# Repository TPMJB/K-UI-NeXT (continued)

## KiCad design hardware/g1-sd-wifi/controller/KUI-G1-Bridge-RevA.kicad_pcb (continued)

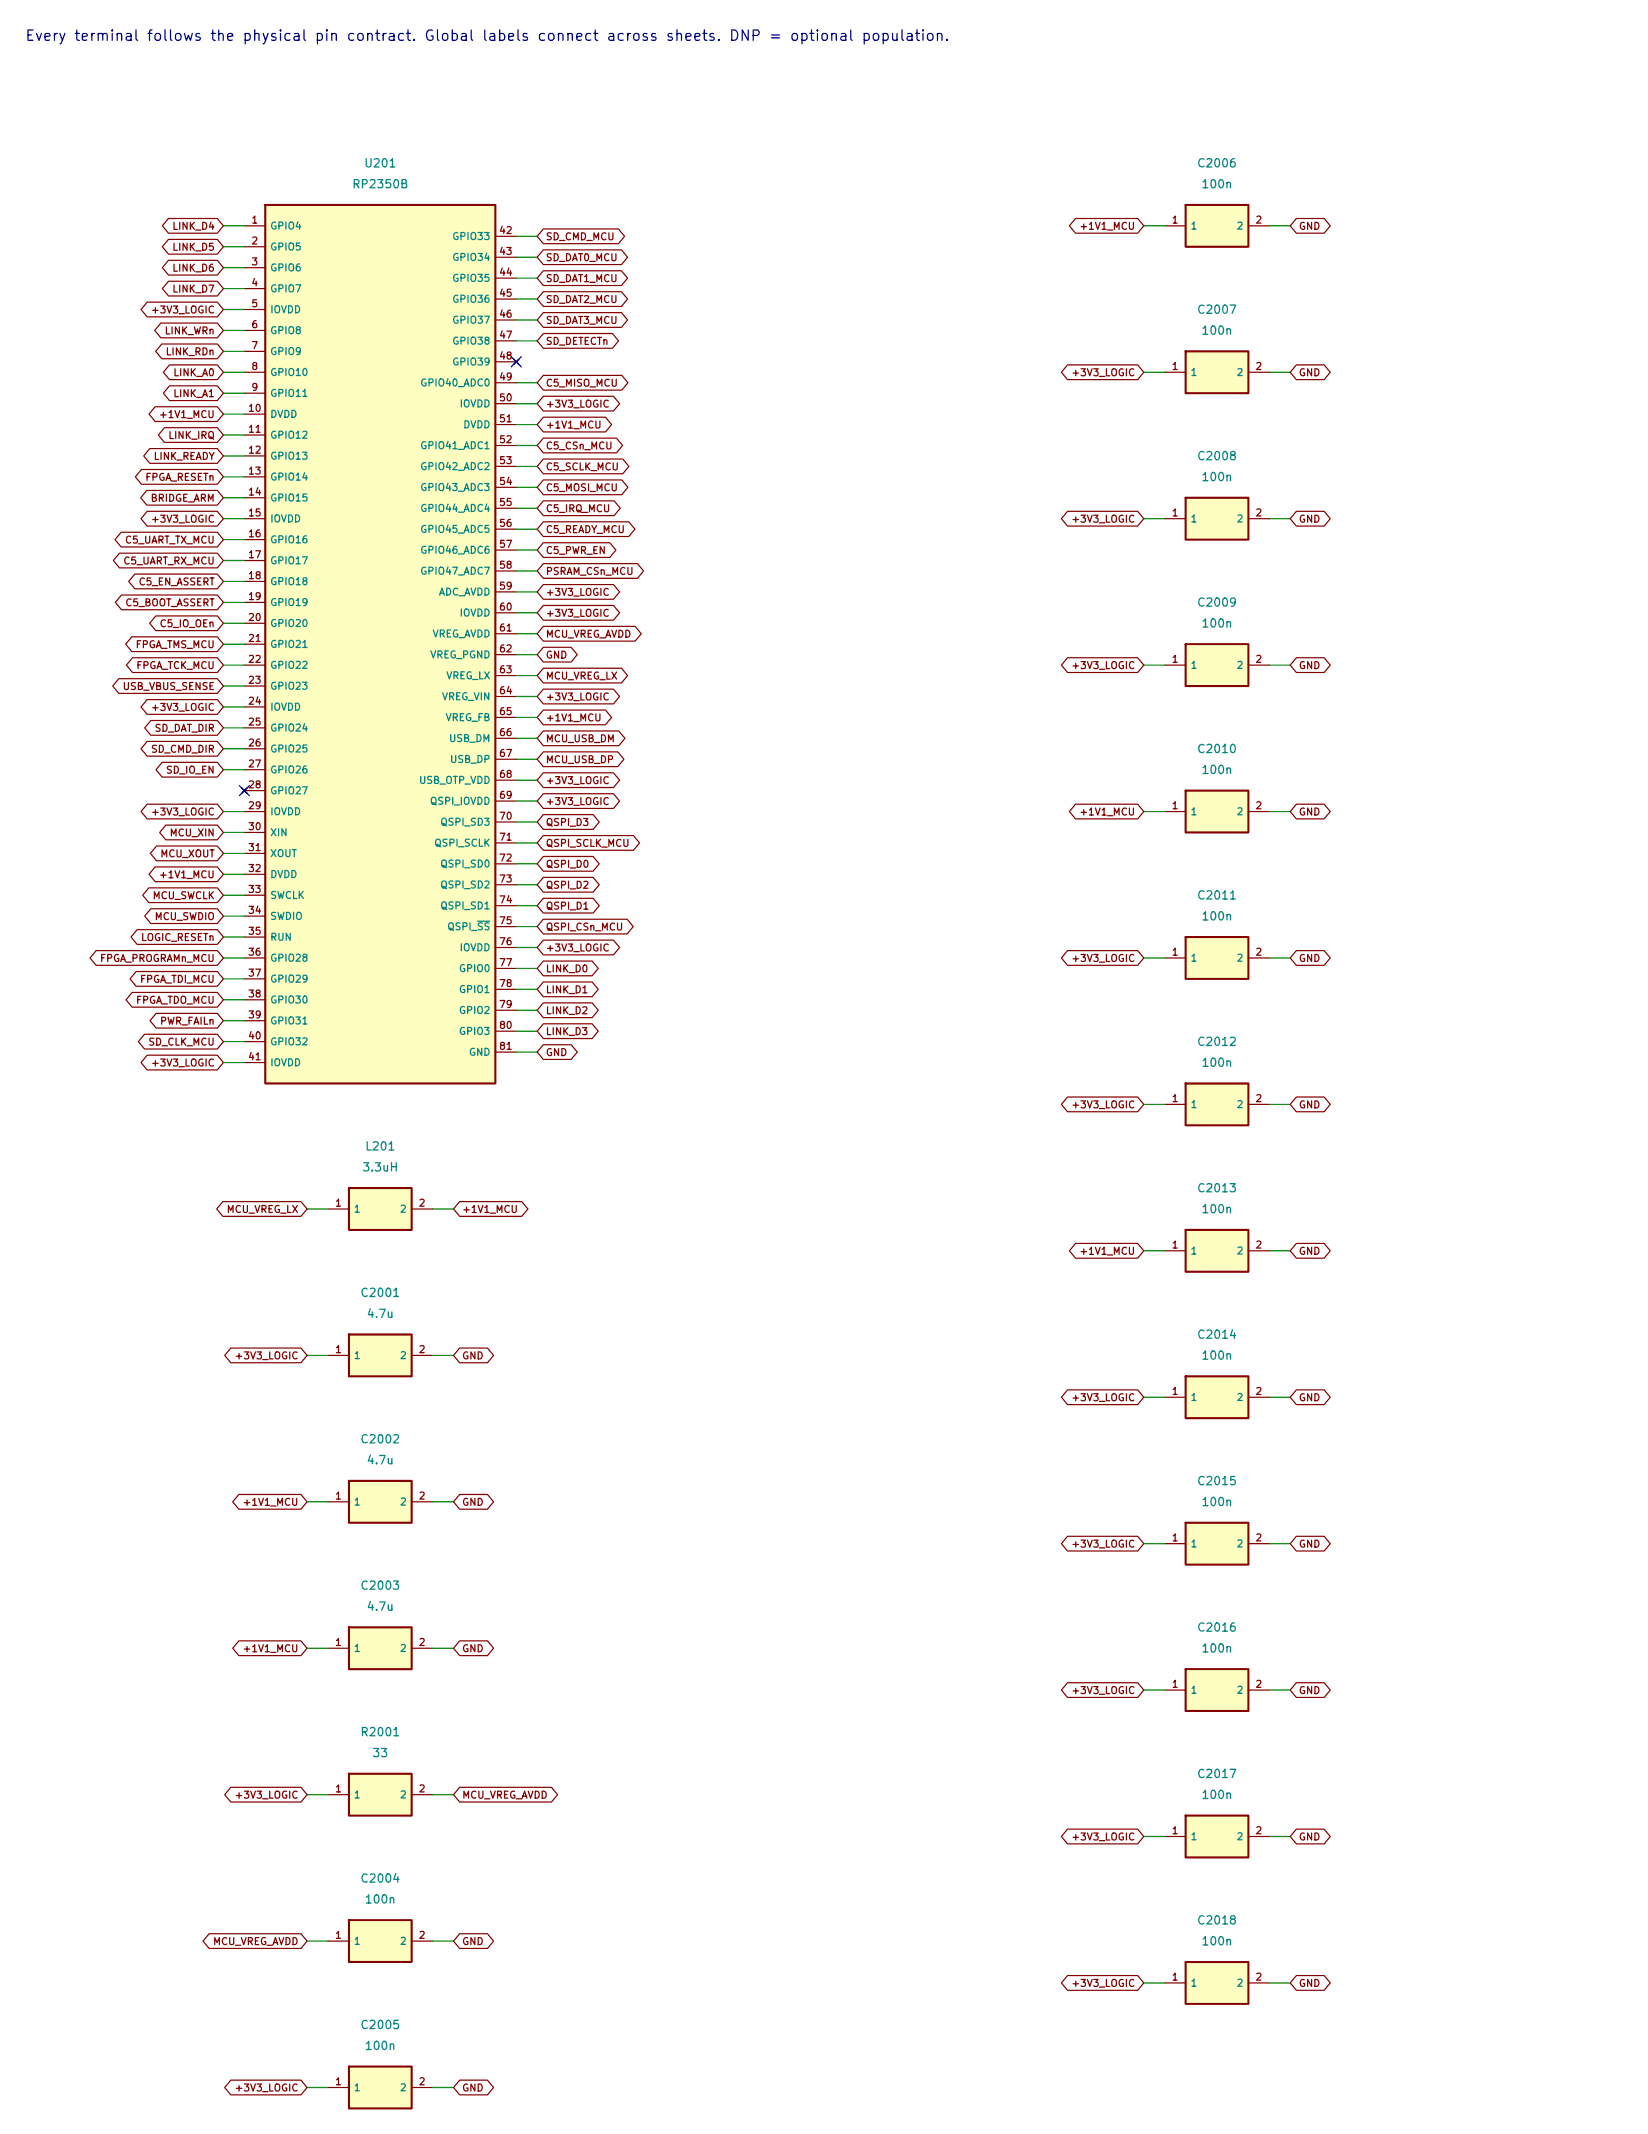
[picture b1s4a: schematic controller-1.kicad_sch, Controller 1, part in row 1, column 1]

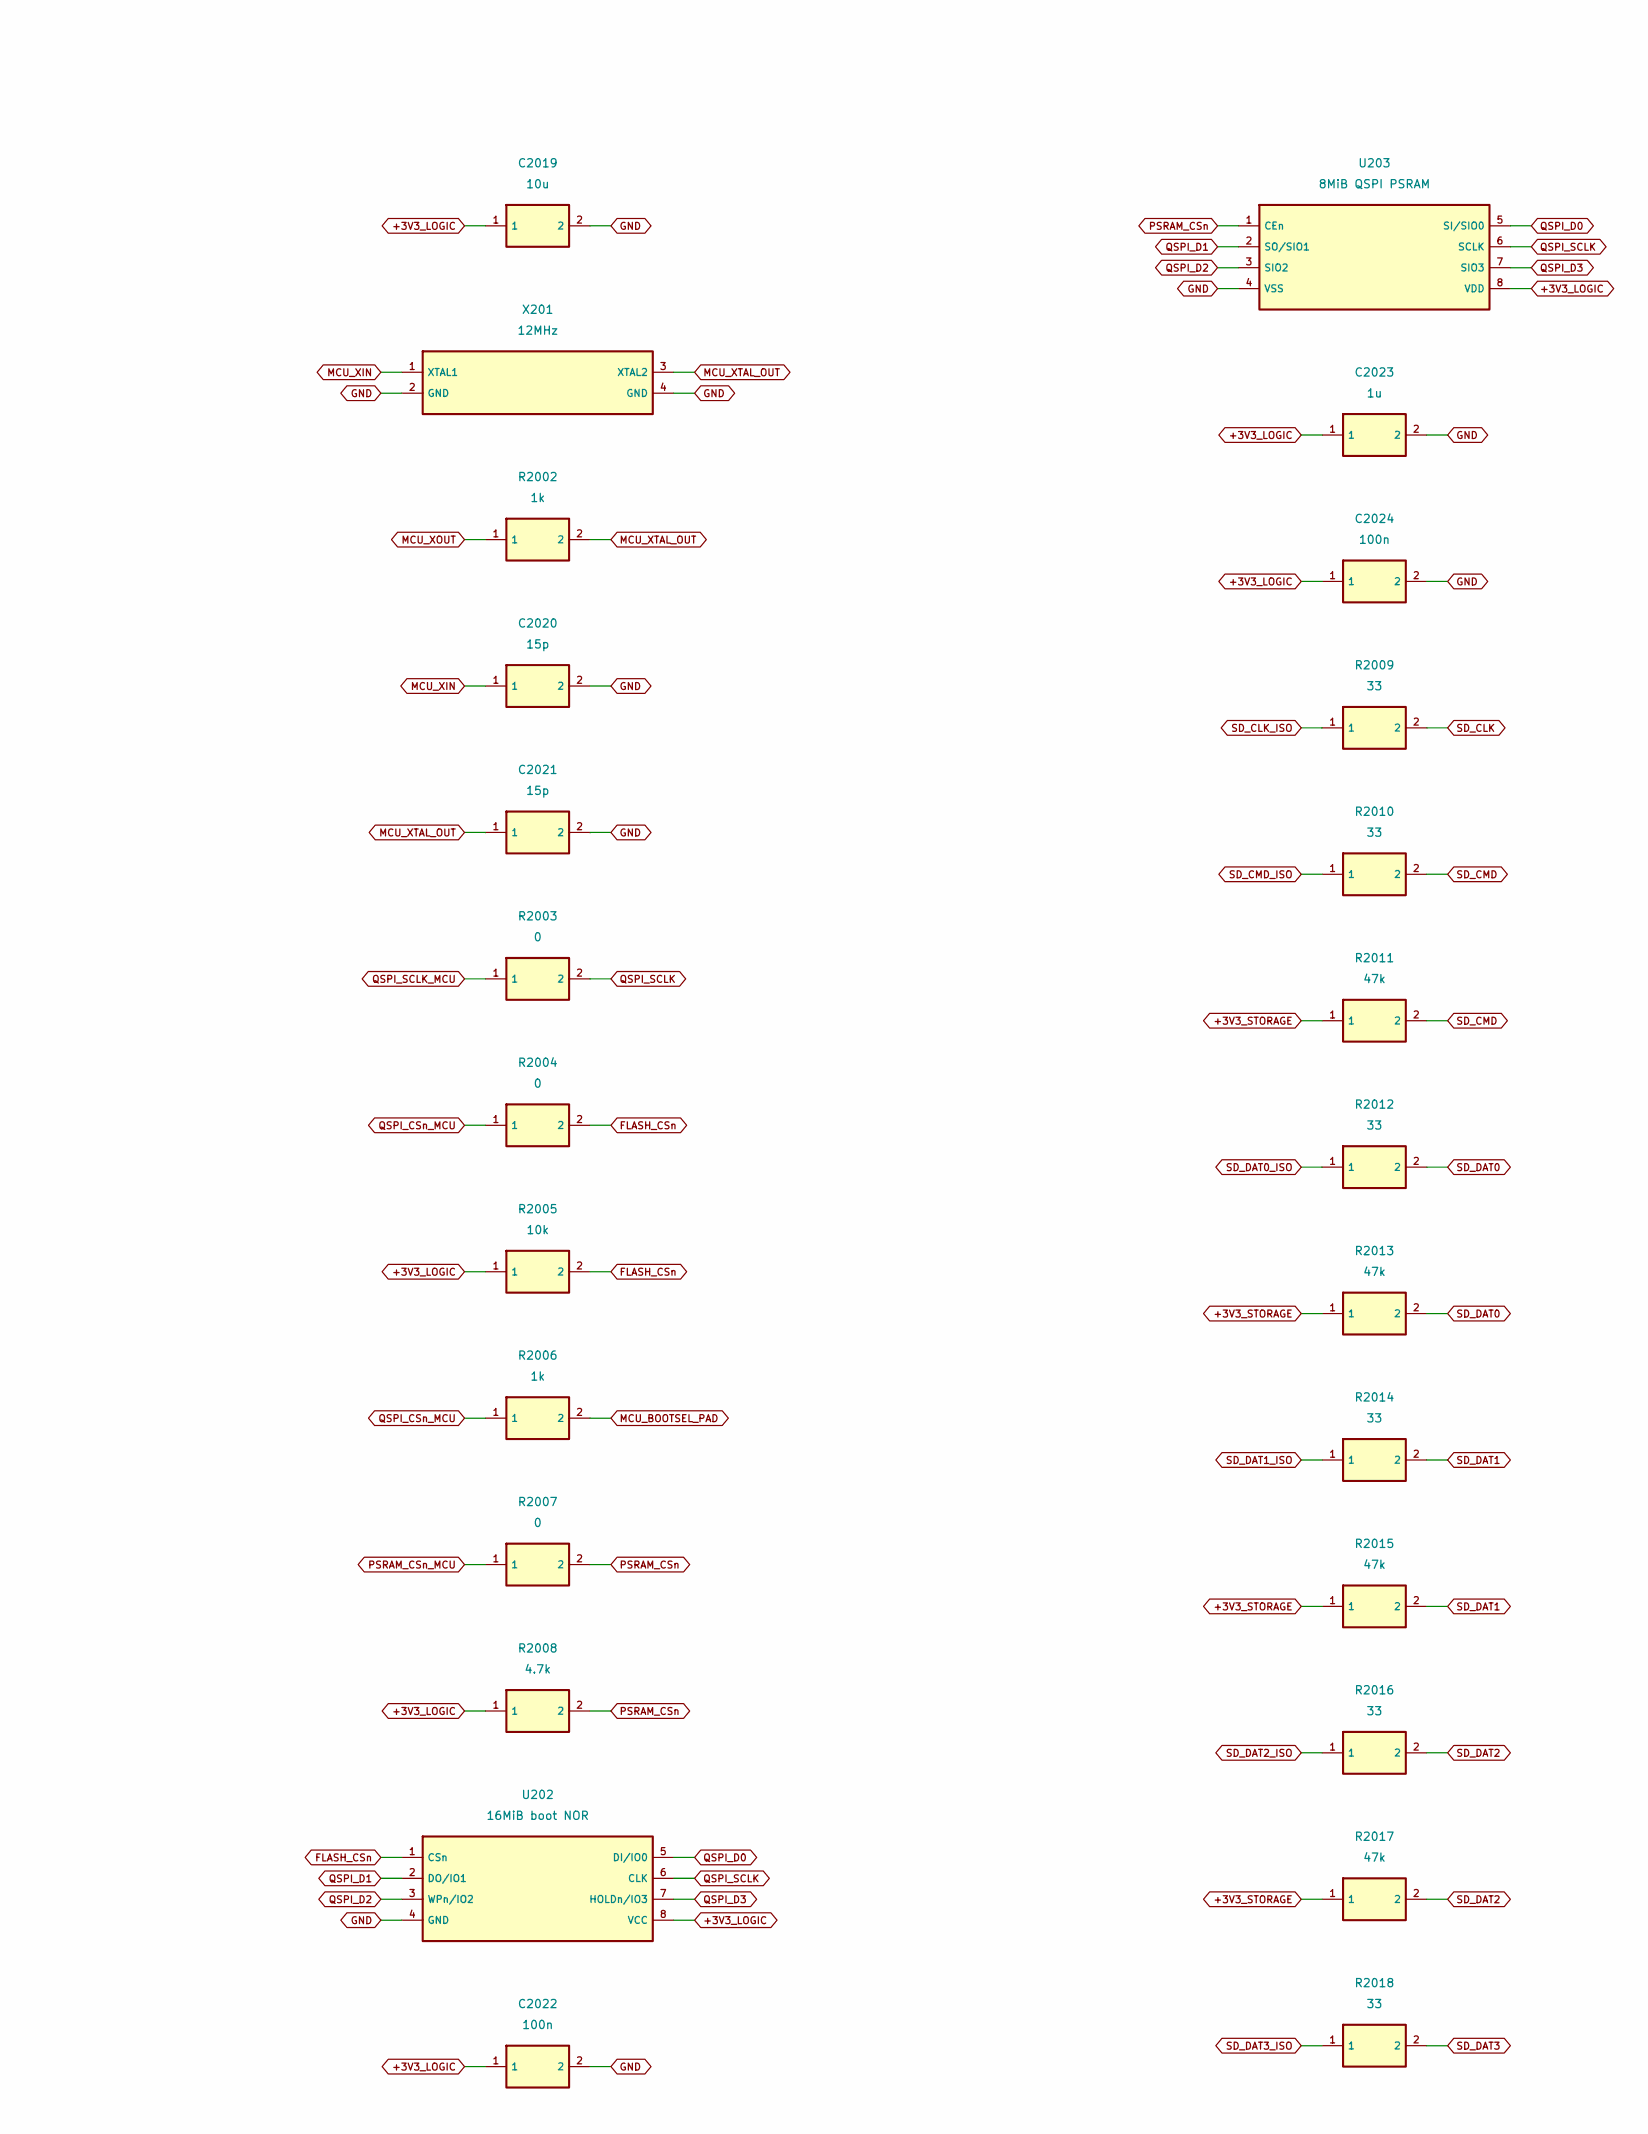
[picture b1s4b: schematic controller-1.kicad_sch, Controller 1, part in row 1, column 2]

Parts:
C2001, C2002, C2003: 4.7u; C_0402_1005Metric; MPN GRM155R60J475ME47D
C2004, C2005, C2006, C2007, C2008, C2009, C2010, C2011, C2012, C2013, C2014, C2015, C2016, C2017, C2018, C2022, C2024: 100n; C_0402_1005Metric; MPN GRM155R71E104KE14D
C2019: 10u; C_0805_2012Metric; MPN GRM21BR61C106KE15L
C2020, C2021: 15p; C_0402_1005Metric; MPN GRM1555C1H150JA01D
C2023: 1u; C_0402_1005Metric; MPN GRM155R61A105KE15D
L201: 3.3uH; AOTA-B201610S3R3-101-T; MPN AOTA-B201610S3R3-101-T
R2001, R2009, R2010, R2012, R2014, R2016, R2018: 33; R_0402_1005Metric; MPN RC0402FR-0733RL
R2002, R2006: 1k; R_0402_1005Metric; MPN RC0402FR-071KL
R2003, R2004, R2007: 0; R_0402_1005Metric; MPN RC0402JR-070RL
R2005: 10k; R_0402_1005Metric; MPN RC0402FR-0710KL
R2008: 4.7k; R_0402_1005Metric; MPN RC0402FR-074K7L
R2011, R2013, R2015, R2017: 47k; R_0402_1005Metric; MPN RC0402FR-0747KL
U201: RP2350B; QFN-80-1EP_10x10mm_P0.4mm_EP3.4x3.4mm_ThermalVias; MPN RP2350B
U202: 16MiB boot NOR; SOIC-8_5.3x5.3mm_P1.27mm; MPN W25Q128JVSIQ
U203: 8MiB QSPI PSRAM; APS6404L_USON8_3x2_P0.5; MPN APS6404L-3SQR-ZR
X201: 12MHz; Crystal_SMD_3225-4Pin_3.2x2.5mm; MPN ABM8-272-T3

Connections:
+1V1_MCU: C2002.1, C2003.1, C2006.1, C2010.1, C2013.1, L201.2, U201.10 (DVDD), U201.32 (DVDD), U201.51 (DVDD), U201.65 (VREG_FB)
+3V3_LOGIC: C2001.1, C2005.1, C2007.1, C2008.1, C2009.1, C2011.1, C2012.1, C2014.1, C2015.1, C2016.1, C2017.1, C2018.1, C2019.1, C2022.1, C2023.1, C2024.1, R2001.1, R2005.1, R2008.1, U201.5 (IOVDD), U201.15 (IOVDD), U201.24 (IOVDD), U201.29 (IOVDD), U201.41 (IOVDD), U201.50 (IOVDD), U201.59 (ADC_AVDD), U201.60 (IOVDD), U201.64 (VREG_VIN), U201.68 (USB_OTP_VDD), U201.69 (QSPI_IOVDD), U201.76 (IOVDD), U202.8 (VCC), U203.8 (VDD); also elsewhere on the board
+3V3_STORAGE: R2011.1, R2013.1, R2015.1, R2017.1; also elsewhere on the board
BRIDGE_ARM: U201.14 (GPIO15); also elsewhere on the board
C5_BOOT_ASSERT: U201.19 (GPIO19); also elsewhere on the board
C5_CSn_MCU: U201.52 (GPIO41_ADC1); also elsewhere on the board
C5_EN_ASSERT: U201.18 (GPIO18); also elsewhere on the board
C5_IO_OEn: U201.20 (GPIO20); also elsewhere on the board
C5_IRQ_MCU: U201.55 (GPIO44_ADC4); also elsewhere on the board
C5_MISO_MCU: U201.49 (GPIO40_ADC0); also elsewhere on the board
C5_MOSI_MCU: U201.54 (GPIO43_ADC3); also elsewhere on the board
C5_PWR_EN: U201.57 (GPIO46_ADC6); also elsewhere on the board
C5_READY_MCU: U201.56 (GPIO45_ADC5); also elsewhere on the board
C5_SCLK_MCU: U201.53 (GPIO42_ADC2); also elsewhere on the board
C5_UART_RX_MCU: U201.17 (GPIO17); also elsewhere on the board
C5_UART_TX_MCU: U201.16 (GPIO16); also elsewhere on the board
FLASH_CSn: R2004.2, R2005.2, U202.1 (CSn)
FPGA_PROGRAMn_MCU: U201.36 (GPIO28); also elsewhere on the board
FPGA_RESETn: U201.13 (GPIO14); also elsewhere on the board
FPGA_TCK_MCU: U201.22 (GPIO22); also elsewhere on the board
FPGA_TDI_MCU: U201.37 (GPIO29); also elsewhere on the board
FPGA_TDO_MCU: U201.38 (GPIO30); also elsewhere on the board
FPGA_TMS_MCU: U201.21 (GPIO21); also elsewhere on the board
GND: C2001.2, C2002.2, C2003.2, C2004.2, C2005.2, C2006.2, C2007.2, C2008.2, C2009.2, C2010.2, C2011.2, C2012.2, C2013.2, C2014.2, C2015.2, C2016.2, C2017.2, C2018.2, C2019.2, C2020.2, C2021.2, C2022.2, C2023.2, C2024.2, U201.62 (VREG_PGND), U201.81 (GND), U202.4 (GND), U203.4 (VSS), X201.2 (GND), X201.4 (GND); also elsewhere on the board
LINK_A0: U201.8 (GPIO10); also elsewhere on the board
LINK_A1: U201.9 (GPIO11); also elsewhere on the board
LINK_D0: U201.77 (GPIO0); also elsewhere on the board
LINK_D1: U201.78 (GPIO1); also elsewhere on the board
LINK_D2: U201.79 (GPIO2); also elsewhere on the board
LINK_D3: U201.80 (GPIO3); also elsewhere on the board
LINK_D4: U201.1 (GPIO4); also elsewhere on the board
LINK_D5: U201.2 (GPIO5); also elsewhere on the board
LINK_D6: U201.3 (GPIO6); also elsewhere on the board
LINK_D7: U201.4 (GPIO7); also elsewhere on the board
LINK_IRQ: U201.11 (GPIO12); also elsewhere on the board
LINK_RDn: U201.7 (GPIO9); also elsewhere on the board
LINK_READY: U201.12 (GPIO13); also elsewhere on the board
LINK_WRn: U201.6 (GPIO8); also elsewhere on the board
LOGIC_RESETn: U201.35 (RUN); also elsewhere on the board
MCU_BOOTSEL_PAD: R2006.2; also elsewhere on the board
MCU_SWCLK: U201.33 (SWCLK); also elsewhere on the board
MCU_SWDIO: U201.34 (SWDIO); also elsewhere on the board
MCU_USB_DM: U201.66 (USB_DM); also elsewhere on the board
MCU_USB_DP: U201.67 (USB_DP); also elsewhere on the board
MCU_VREG_AVDD: C2004.1, R2001.2, U201.61 (VREG_AVDD)
MCU_VREG_LX: L201.1, U201.63 (VREG_LX)
MCU_XIN: C2020.1, U201.30 (XIN), X201.1 (XTAL1)
MCU_XOUT: R2002.1, U201.31 (XOUT)
MCU_XTAL_OUT: C2021.1, R2002.2, X201.3 (XTAL2)
PSRAM_CSn: R2007.2, R2008.2, U203.1 (CEn)
PSRAM_CSn_MCU: R2007.1, U201.58 (GPIO47_ADC7)
PWR_FAILn: U201.39 (GPIO31); also elsewhere on the board
QSPI_CSn_MCU: R2004.1, R2006.1, U201.75 (QSPI_~SS)
QSPI_D0: U201.72 (QSPI_SD0), U202.5 (DI/IO0), U203.5 (SI/SIO0)
QSPI_D1: U201.74 (QSPI_SD1), U202.2 (DO/IO1), U203.2 (SO/SIO1)
QSPI_D2: U201.73 (QSPI_SD2), U202.3 (WPn/IO2), U203.3 (SIO2)
QSPI_D3: U201.70 (QSPI_SD3), U202.7 (HOLDn/IO3), U203.7 (SIO3)
QSPI_SCLK: R2003.2, U202.6 (CLK), U203.6 (SCLK)
QSPI_SCLK_MCU: R2003.1, U201.71 (QSPI_SCLK)
SD_CLK: R2009.2; also elsewhere on the board
SD_CLK_ISO: R2009.1; also elsewhere on the board
SD_CLK_MCU: U201.40 (GPIO32); also elsewhere on the board
SD_CMD: R2010.2, R2011.2; also elsewhere on the board
SD_CMD_DIR: U201.26 (GPIO25); also elsewhere on the board
SD_CMD_ISO: R2010.1; also elsewhere on the board
SD_CMD_MCU: U201.42 (GPIO33); also elsewhere on the board
SD_DAT0: R2012.2, R2013.2; also elsewhere on the board
SD_DAT0_ISO: R2012.1; also elsewhere on the board
SD_DAT0_MCU: U201.43 (GPIO34); also elsewhere on the board
SD_DAT1: R2014.2, R2015.2; also elsewhere on the board
SD_DAT1_ISO: R2014.1; also elsewhere on the board
SD_DAT1_MCU: U201.44 (GPIO35); also elsewhere on the board
SD_DAT2: R2016.2, R2017.2; also elsewhere on the board
SD_DAT2_ISO: R2016.1; also elsewhere on the board
SD_DAT2_MCU: U201.45 (GPIO36); also elsewhere on the board
SD_DAT3: R2018.2; also elsewhere on the board
SD_DAT3_ISO: R2018.1; also elsewhere on the board
SD_DAT3_MCU: U201.46 (GPIO37); also elsewhere on the board
SD_DAT_DIR: U201.25 (GPIO24); also elsewhere on the board
SD_DETECTn: U201.47 (GPIO38); also elsewhere on the board
SD_IO_EN: U201.27 (GPIO26); also elsewhere on the board
USB_VBUS_SENSE: U201.23 (GPIO23); also elsewhere on the board

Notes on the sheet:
Every terminal follows the physical pin contract. Global labels connect across sheets. DNP = optional population.

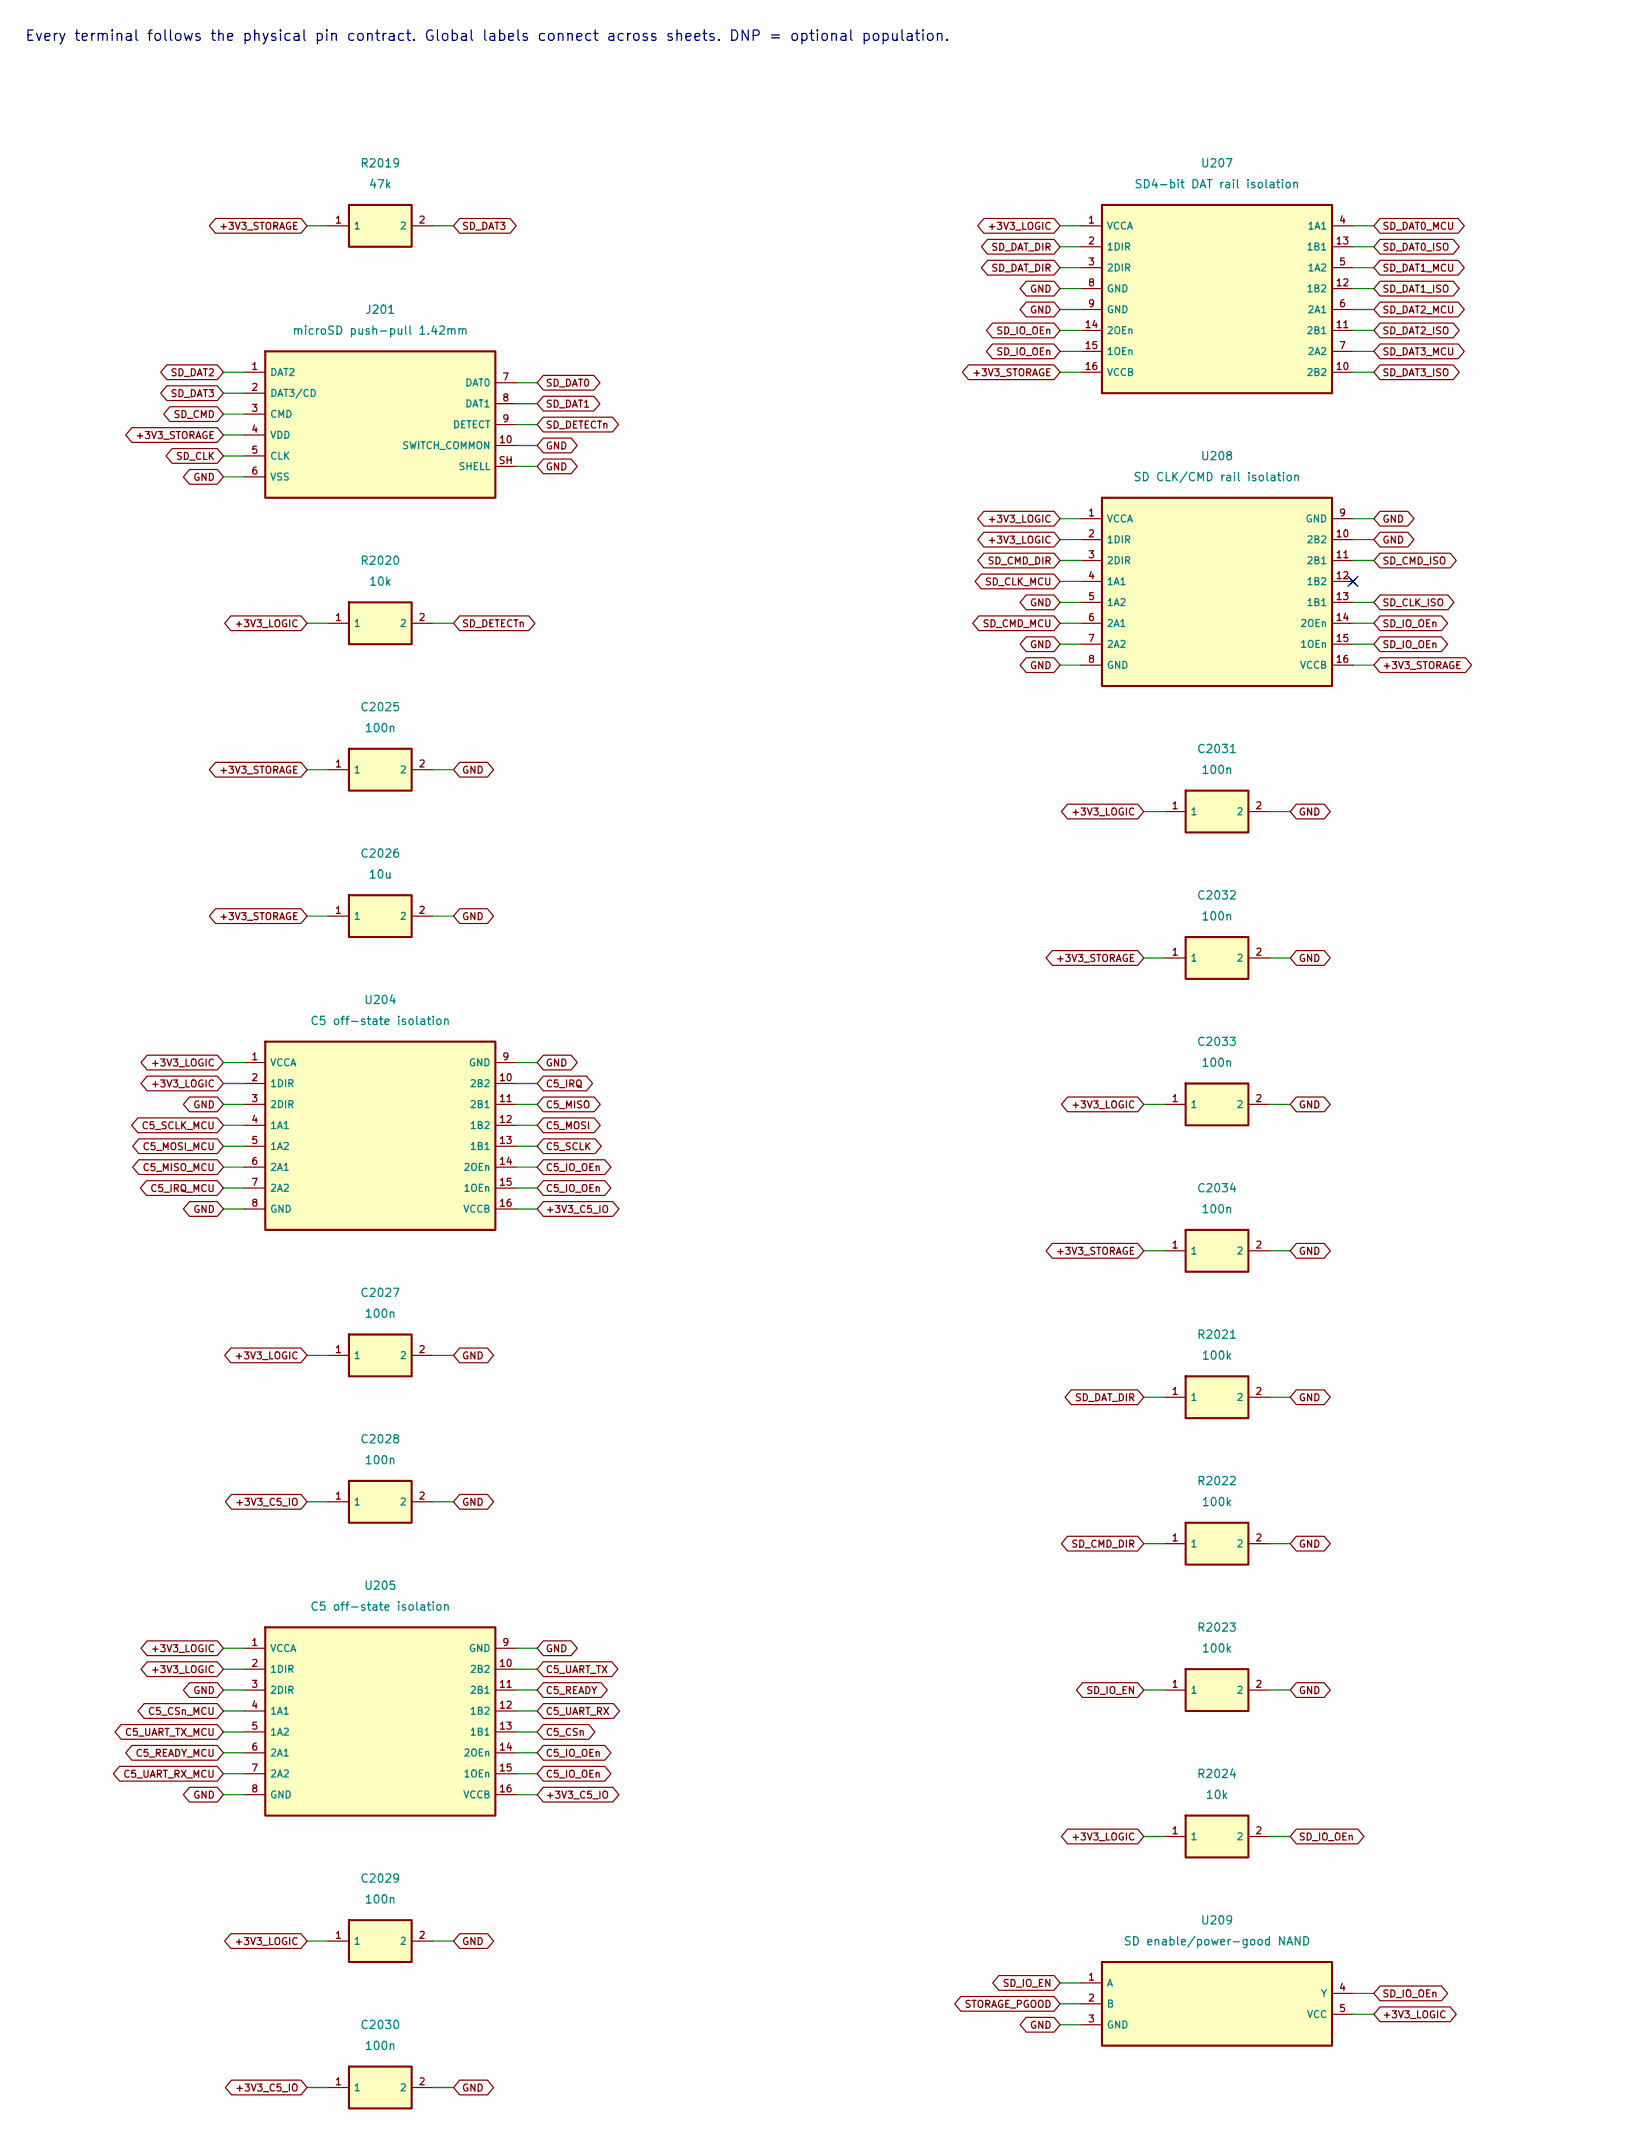
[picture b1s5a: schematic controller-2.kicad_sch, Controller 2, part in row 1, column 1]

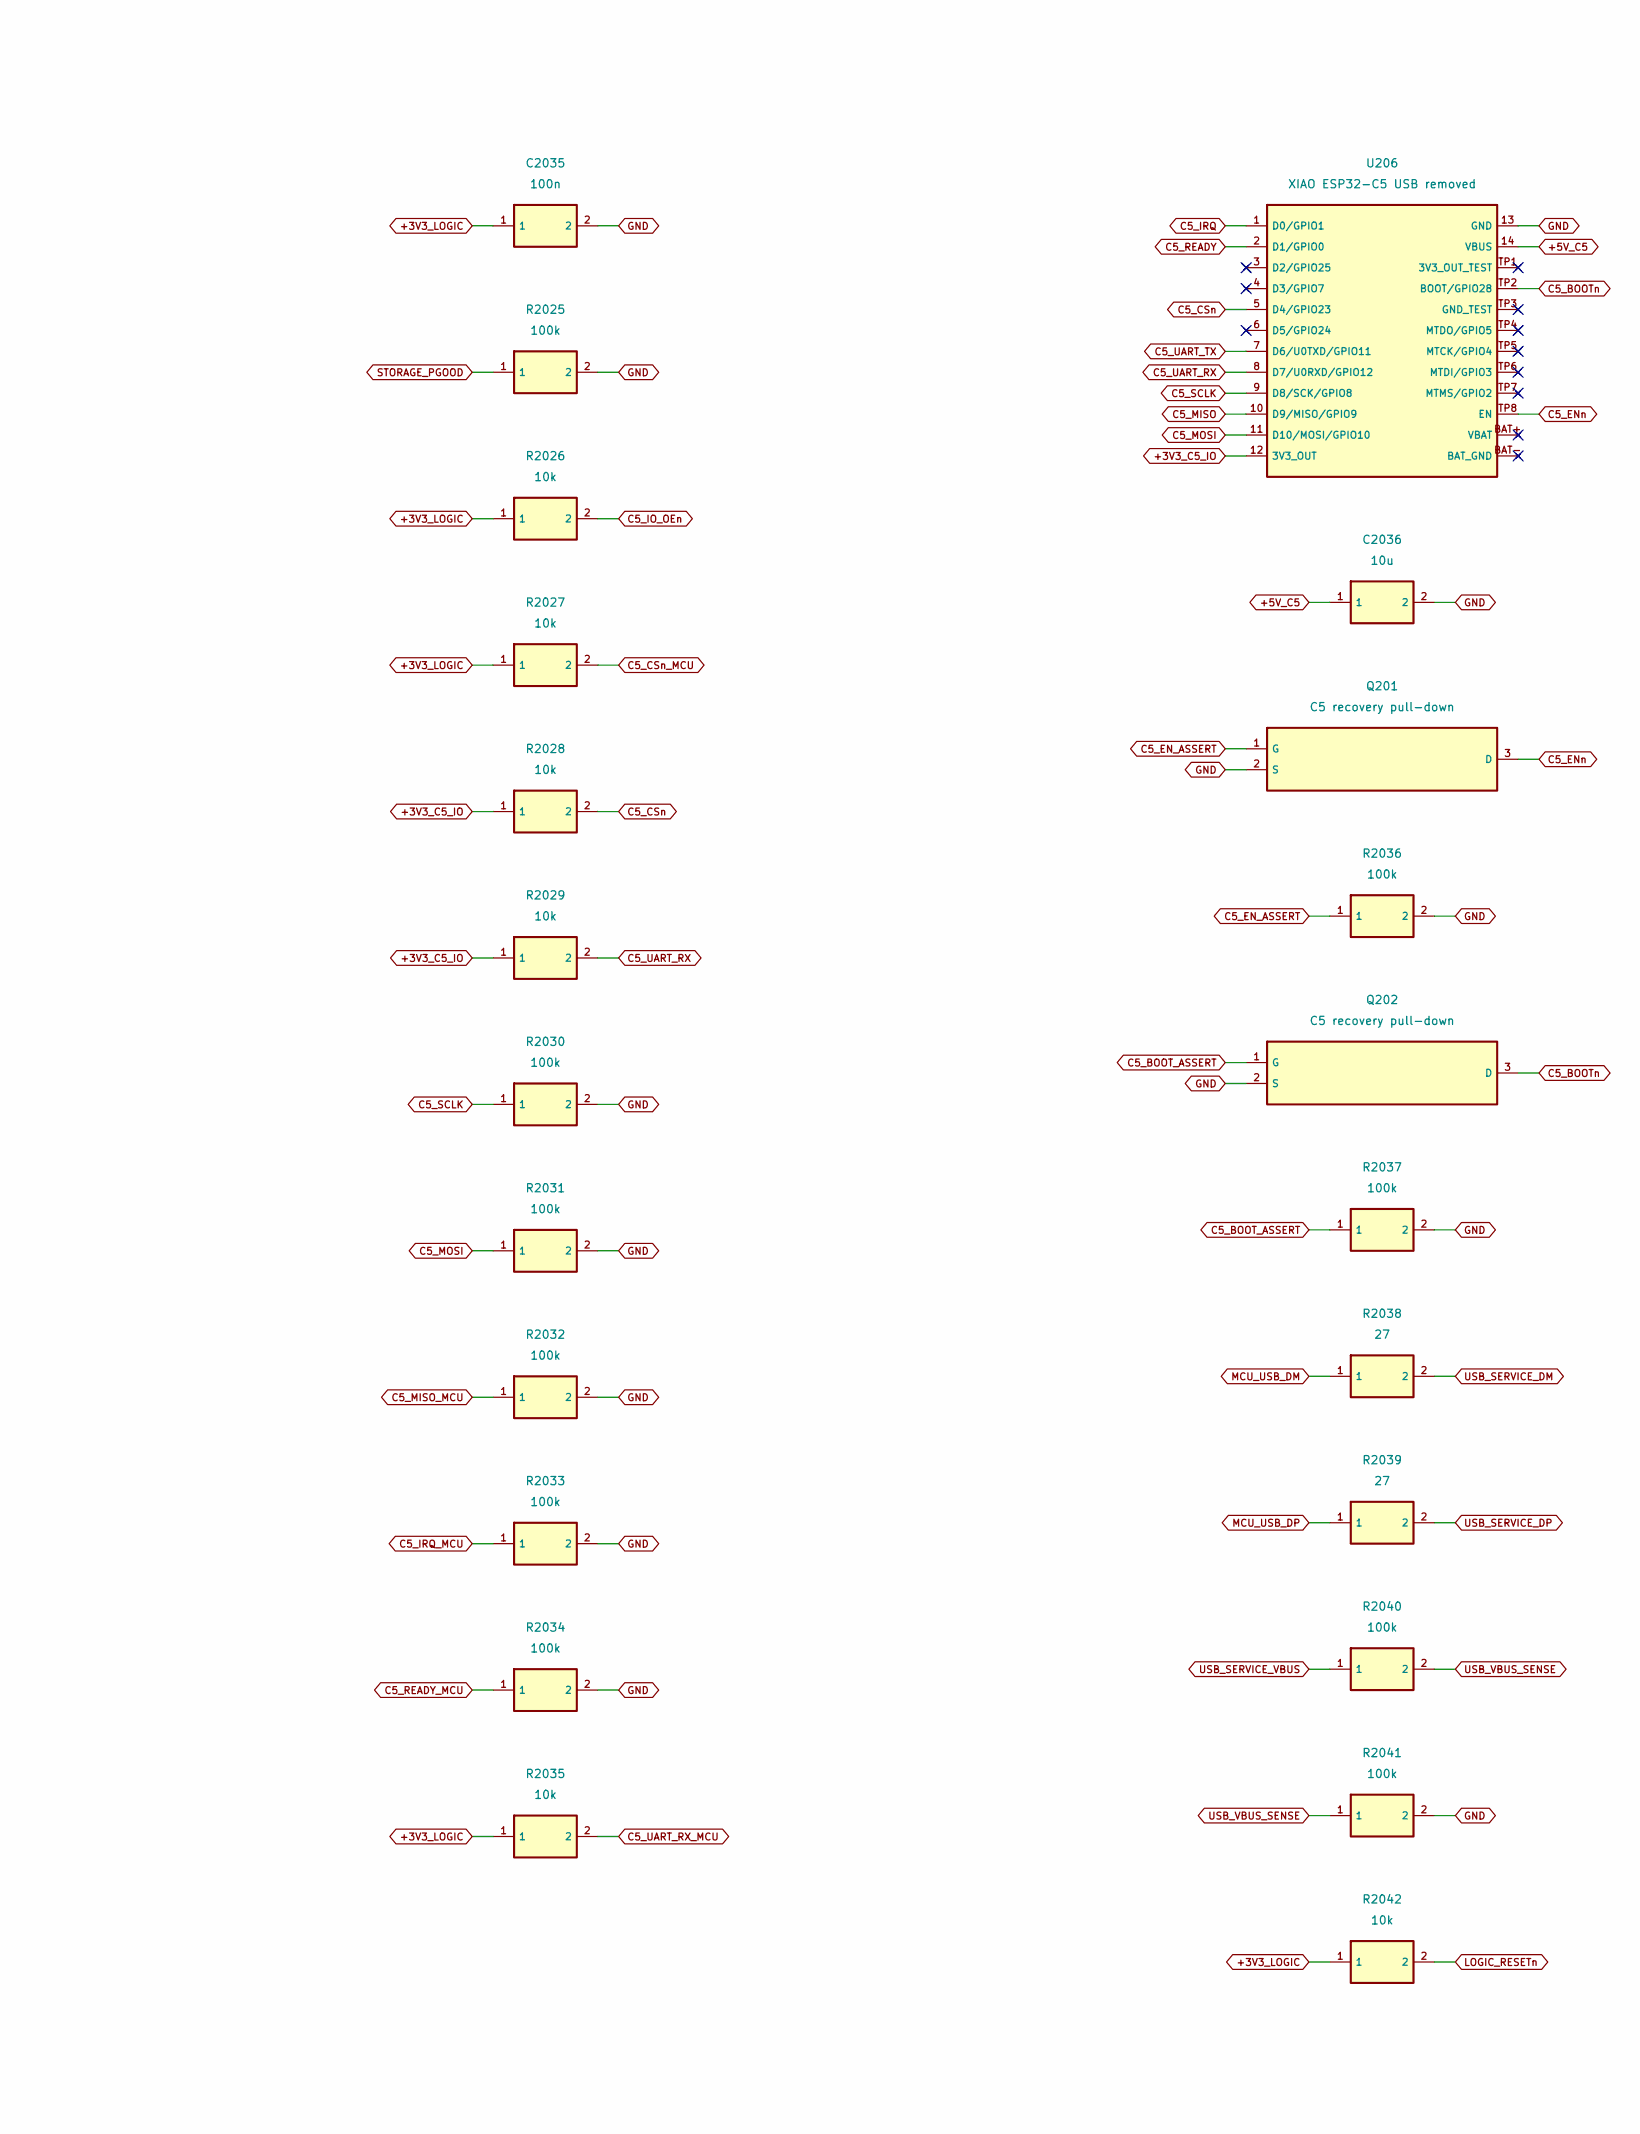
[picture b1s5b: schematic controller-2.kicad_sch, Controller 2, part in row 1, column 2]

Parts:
C2025, C2027, C2028, C2029, C2030, C2031, C2032, C2033, C2034, C2035: 100n; C_0402_1005Metric; MPN GRM155R71E104KE14D
C2026, C2036: 10u; C_0805_2012Metric; MPN GRM21BR61C106KE15L
J201: microSD push-pull 1.42mm; microSD_HC_Molex_104031-0811; MPN 1040310811
Q201, Q202: C5 recovery pull-down; SOT-23; MPN 2N7002,215
R2019: 47k; R_0402_1005Metric; MPN RC0402FR-0747KL
R2020, R2024, R2026, R2027, R2028, R2029, R2035, R2042: 10k; R_0402_1005Metric; MPN RC0402FR-0710KL
R2021, R2022, R2023, R2025, R2030, R2031, R2032, R2033, R2034, R2036, R2037, R2040, R2041: 100k; R_0402_1005Metric; MPN RC0402FR-07100KL
R2038, R2039: 27; R_0402_1005Metric; MPN RC0402FR-0727RL
U204, U205: C5 off-state isolation; TSSOP-16_4.4x5mm_P0.65mm; MPN SN74AXC4T245PWR
U206: XIAO ESP32-C5 USB removed; MPN 100010048
U207: SD4-bit DAT rail isolation; TSSOP-16_4.4x5mm_P0.65mm; MPN SN74AXC4T245PWR
U208: SD CLK/CMD rail isolation; TSSOP-16_4.4x5mm_P0.65mm; MPN SN74AXC4T245PWR
U209: SD enable/power-good NAND; SOT-23-5; MPN SN74LVC1G00DBVR

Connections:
+3V3_C5_IO: C2028.1, C2030.1, R2028.1, R2029.1, U204.16 (VCCB), U205.16 (VCCB), U206.12 (3V3_OUT); also elsewhere on the board
+3V3_LOGIC: C2027.1, C2029.1, C2031.1, C2033.1, C2035.1, R2020.1, R2024.1, R2026.1, R2027.1, R2035.1, R2042.1, U204.1 (VCCA), U204.2 (1DIR), U205.1 (VCCA), U205.2 (1DIR), U207.1 (VCCA), U208.1 (VCCA), U208.2 (1DIR), U209.5 (VCC); also elsewhere on the board
+3V3_STORAGE: C2025.1, C2026.1, C2032.1, C2034.1, J201.4 (VDD), R2019.1, U207.16 (VCCB), U208.16 (VCCB); also elsewhere on the board
+5V_C5: C2036.1, U206.14 (VBUS); also elsewhere on the board
C5_BOOT_ASSERT: Q202.1 (G), R2037.1; also elsewhere on the board
C5_BOOTn: Q202.3 (D), U206.TP2 (BOOT/GPIO28); also elsewhere on the board
C5_CSn: R2028.2, U205.13 (1B1), U206.5 (D4/GPIO23); also elsewhere on the board
C5_CSn_MCU: R2027.2, U205.4 (1A1); also elsewhere on the board
C5_EN_ASSERT: Q201.1 (G), R2036.1; also elsewhere on the board
C5_ENn: Q201.3 (D), U206.TP8 (EN); also elsewhere on the board
C5_IO_OEn: R2026.2, U204.14 (2OEn), U204.15 (1OEn), U205.14 (2OEn), U205.15 (1OEn); also elsewhere on the board
C5_IRQ: U204.10 (2B2), U206.1 (D0/GPIO1); also elsewhere on the board
C5_IRQ_MCU: R2033.1, U204.7 (2A2); also elsewhere on the board
C5_MISO: U204.11 (2B1), U206.10 (D9/MISO/GPIO9); also elsewhere on the board
C5_MISO_MCU: R2032.1, U204.6 (2A1); also elsewhere on the board
C5_MOSI: R2031.1, U204.12 (1B2), U206.11 (D10/MOSI/GPIO10); also elsewhere on the board
C5_MOSI_MCU: U204.5 (1A2); also elsewhere on the board
C5_READY: U205.11 (2B1), U206.2 (D1/GPIO0); also elsewhere on the board
C5_READY_MCU: R2034.1, U205.6 (2A1); also elsewhere on the board
C5_SCLK: R2030.1, U204.13 (1B1), U206.9 (D8/SCK/GPIO8); also elsewhere on the board
C5_SCLK_MCU: U204.4 (1A1); also elsewhere on the board
C5_UART_RX: R2029.2, U205.12 (1B2), U206.8 (D7/U0RXD/GPIO12); also elsewhere on the board
C5_UART_RX_MCU: R2035.2, U205.7 (2A2); also elsewhere on the board
C5_UART_TX: U205.10 (2B2), U206.7 (D6/U0TXD/GPIO11); also elsewhere on the board
C5_UART_TX_MCU: U205.5 (1A2); also elsewhere on the board
GND: C2025.2, C2026.2, C2027.2, C2028.2, C2029.2, C2030.2, C2031.2, C2032.2, C2033.2, C2034.2, C2035.2, C2036.2, J201.6 (VSS), J201.10 (SWITCH_COMMON), J201.SH (SHELL), Q201.2 (S), Q202.2 (S), R2021.2, R2022.2, R2023.2, R2025.2, R2030.2, R2031.2, R2032.2, R2033.2, R2034.2, R2036.2, R2037.2, R2041.2, U204.3 (2DIR), U204.8 (GND), U204.9 (GND), U205.3 (2DIR), U205.8 (GND), U205.9 (GND), U206.13 (GND), U207.8 (GND), U207.9 (GND), U208.5 (1A2), U208.7 (2A2), U208.8 (GND), U208.9 (GND), U208.10 (2B2), U209.3 (GND); also elsewhere on the board
LOGIC_RESETn: R2042.2; also elsewhere on the board
MCU_USB_DM: R2038.1; also elsewhere on the board
MCU_USB_DP: R2039.1; also elsewhere on the board
SD_CLK: J201.5 (CLK); also elsewhere on the board
SD_CLK_ISO: U208.13 (1B1); also elsewhere on the board
SD_CLK_MCU: U208.4 (1A1); also elsewhere on the board
SD_CMD: J201.3 (CMD); also elsewhere on the board
SD_CMD_DIR: R2022.1, U208.3 (2DIR); also elsewhere on the board
SD_CMD_ISO: U208.11 (2B1); also elsewhere on the board
SD_CMD_MCU: U208.6 (2A1); also elsewhere on the board
SD_DAT0: J201.7 (DAT0); also elsewhere on the board
SD_DAT0_ISO: U207.13 (1B1); also elsewhere on the board
SD_DAT0_MCU: U207.4 (1A1); also elsewhere on the board
SD_DAT1: J201.8 (DAT1); also elsewhere on the board
SD_DAT1_ISO: U207.12 (1B2); also elsewhere on the board
SD_DAT1_MCU: U207.5 (1A2); also elsewhere on the board
SD_DAT2: J201.1 (DAT2); also elsewhere on the board
SD_DAT2_ISO: U207.11 (2B1); also elsewhere on the board
SD_DAT2_MCU: U207.6 (2A1); also elsewhere on the board
SD_DAT3: J201.2 (DAT3/CD), R2019.2; also elsewhere on the board
SD_DAT3_ISO: U207.10 (2B2); also elsewhere on the board
SD_DAT3_MCU: U207.7 (2A2); also elsewhere on the board
SD_DAT_DIR: R2021.1, U207.2 (1DIR), U207.3 (2DIR); also elsewhere on the board
SD_DETECTn: J201.9 (DETECT), R2020.2; also elsewhere on the board
SD_IO_EN: R2023.1, U209.1 (A); also elsewhere on the board
SD_IO_OEn: R2024.2, U207.14 (2OEn), U207.15 (1OEn), U208.14 (2OEn), U208.15 (1OEn), U209.4 (Y)
STORAGE_PGOOD: R2025.1, U209.2 (B); also elsewhere on the board
USB_SERVICE_DM: R2038.2; also elsewhere on the board
USB_SERVICE_DP: R2039.2; also elsewhere on the board
USB_SERVICE_VBUS: R2040.1; also elsewhere on the board
USB_VBUS_SENSE: R2040.2, R2041.1; also elsewhere on the board

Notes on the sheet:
Every terminal follows the physical pin contract. Global labels connect across sheets. DNP = optional population.
